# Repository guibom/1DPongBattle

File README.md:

1DPongBattle
============

Pong game with LED strips and wireless pedal controllers

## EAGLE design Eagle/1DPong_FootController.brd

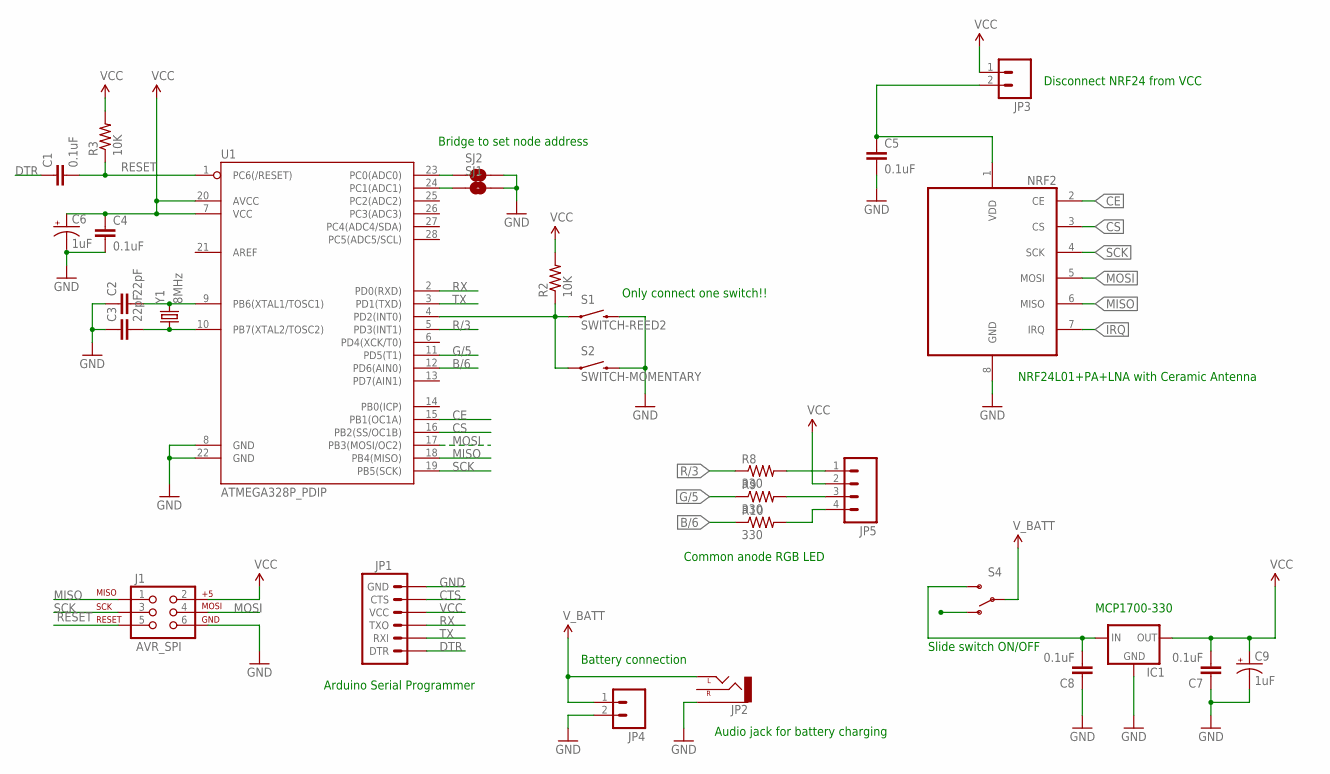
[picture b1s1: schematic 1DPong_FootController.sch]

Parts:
C1, C4, C5, C7, C8: 0.1uF; CAP-PTH-SMALL
C2, C3: 22pF; CAP-PTH-SMALL
C6, C9: 1uF; CPOL-RADIAL-10UF-25V
IC1: V_REG_78XXTO-92_UNTESTED; TO-92
J1: AVR_SPI; 2X3
JP1: ARDUINO_SERIAL_PROGRAMPTH; 1X06
JP2: AUDIO-JACKPTH; AUDIO-JACK
JP3, JP4: M02PTH; 1X02
JP5: M04PTH; 1X04
NRF2: NRF24L01_SOIC
R2, R3: 10K; 1206
R8, R9, R10: 330; 1206
S1: SWITCH-REED2; REED_SWITCH_PLASTIC
S2: SWITCH-MOMENTARY; TACTILE-PTH
S4: SWITCH-SPDT-SMD-A; SWITCH-SPST-SMD-A
SJ1, SJ2: JUMPER-PAD-2-NOYES_SILK; PAD-JUMPER-2-NO_YES_SILK
U1: ATMEGA328P_PDIP; DIL28-3
Y1: 8MHz; HC49US

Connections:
B/6: R10.1, U1.12 (PD6(AIN0))
CE: NRF2.2 (CE), U1.15 (PB1(OC1A))
CS: NRF2.3 (CS), U1.16 (PB2(SS/OC1B))
CTS: JP1.CTS
DTR: C1.1, JP1.DTR
G/5: R9.1, U1.11 (PD5(T1))
GND: C2.1, C3.1, C4.2, C5.2, C6.2 (-), C7.1, C8.1, C9.2 (-), IC1.1 (GND), J1.6, JP1.GND, JP2.SLEEVE, JP4.2, NRF2.8 (GND), S1.P$2 (2), S2.3 (2), SJ1.2, SJ2.2, U1.8 (GND), U1.22 (GND)
IRQ: NRF2.7 (IRQ)
MISO: J1.1, NRF2.6 (MISO), U1.18 (PB4(MISO))
MOSI: J1.4, NRF2.5 (MOSI), U1.17 (PB3(MOSI/OC2))
unnamed: C2.2, U1.9 (PB6(XTAL1/TOSC1)), Y1.2
unnamed: C3.2, U1.10 (PB7(XTAL2/TOSC2)), Y1.1
unnamed: JP5.1, R8.2
unnamed: SJ2.1, U1.23 (PC0(ADC0))
unnamed: SJ1.1, U1.24 (PC1(ADC1))
unnamed: JP5.3, R9.2
unnamed: R2.1, S1.P$1 (1), S2.1, U1.4 (PD2(INT0))
unnamed: C5.1, JP3.2, NRF2.1 (VDD)
unnamed: JP5.4, R10.2
unnamed: C8.2, IC1.2 (IN), S4.3 (S)
R/3: R8.1, U1.5 (PD3(INT1))
RESET: C1.2, J1.5, R3.1, U1.1 (PC6(/RESET))
RX: JP1.TXO, U1.2 (PD0(RXD))
SCK: J1.3, NRF2.4 (SCK), U1.19 (PB5(SCK))
TX: JP1.RXI, U1.3 (PD1(TXD))
VCC: C4.1, C6.1 (+), C7.2, C9.1 (+), IC1.3 (OUT), J1.2, JP1.VCC, JP3.1, JP5.2, R2.2, R3.2, U1.7 (VCC), U1.20 (AVCC)
V_BATT: JP2.TIP (LEFT), JP4.1, S4.2

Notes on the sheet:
NRF24L01+PA+LNA with Ceramic Antenna
Disconnect NRF24 from VCC
Bridge to set node address
Common anode RGB LED
Audio jack for battery charging
Battery connection
Slide switch ON/OFF
Arduino Serial Programmer
MCP1700-330
Only connect one switch!!

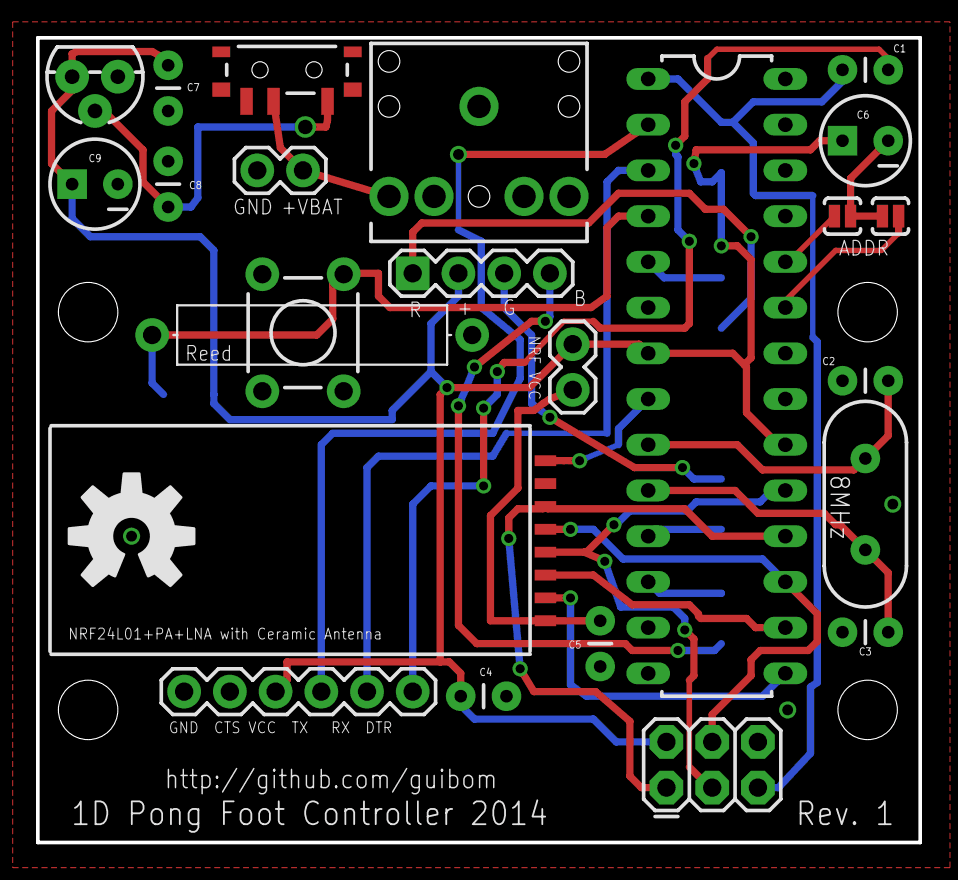
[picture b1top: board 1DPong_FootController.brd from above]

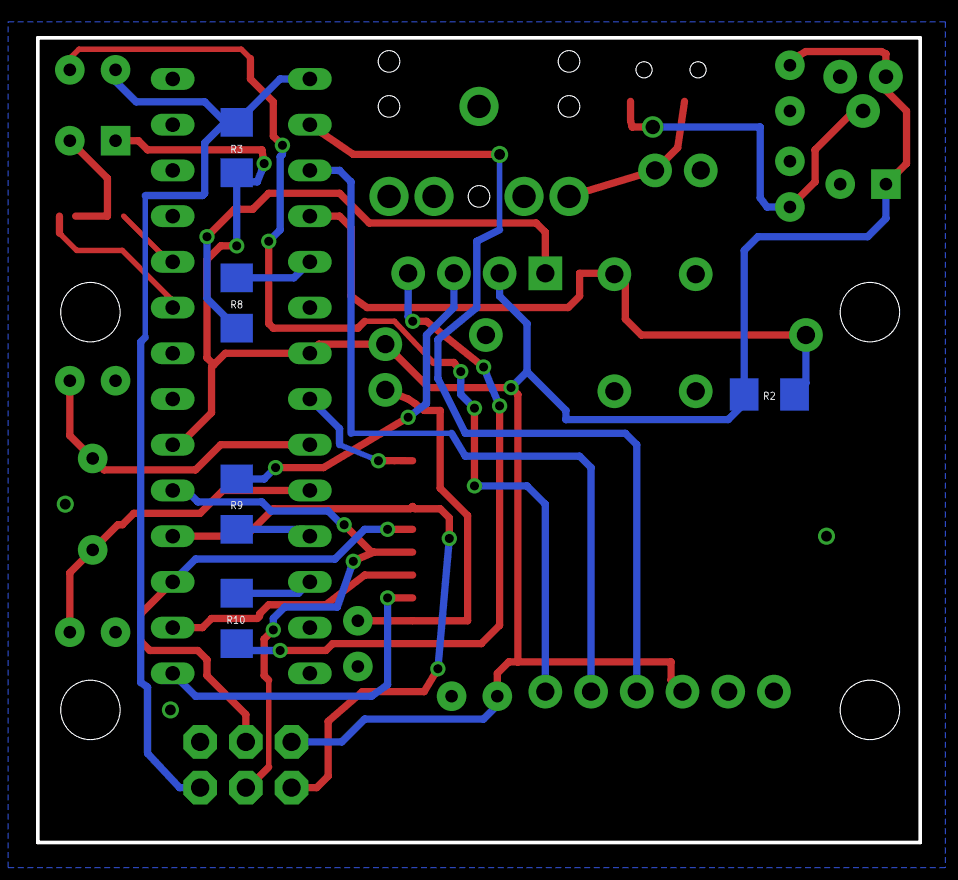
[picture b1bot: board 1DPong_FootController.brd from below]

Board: 2 copper layers, 49.0 x 44.7 mm, 34 parts (5 on the bottom side), 25 nets.

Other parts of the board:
U$1, U$2, U$3, U$4: STAND-OFF
U$5: OSHW-LOGO-L

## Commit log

2014-10-14 Adding eagle files and gerbers

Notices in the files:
parts and their libraries:
SparkFun-DigitalIC: Licensing: Creative Commons ShareAlike 4.0 International - https://creativecommons.org/licenses/by-sa/4.0
